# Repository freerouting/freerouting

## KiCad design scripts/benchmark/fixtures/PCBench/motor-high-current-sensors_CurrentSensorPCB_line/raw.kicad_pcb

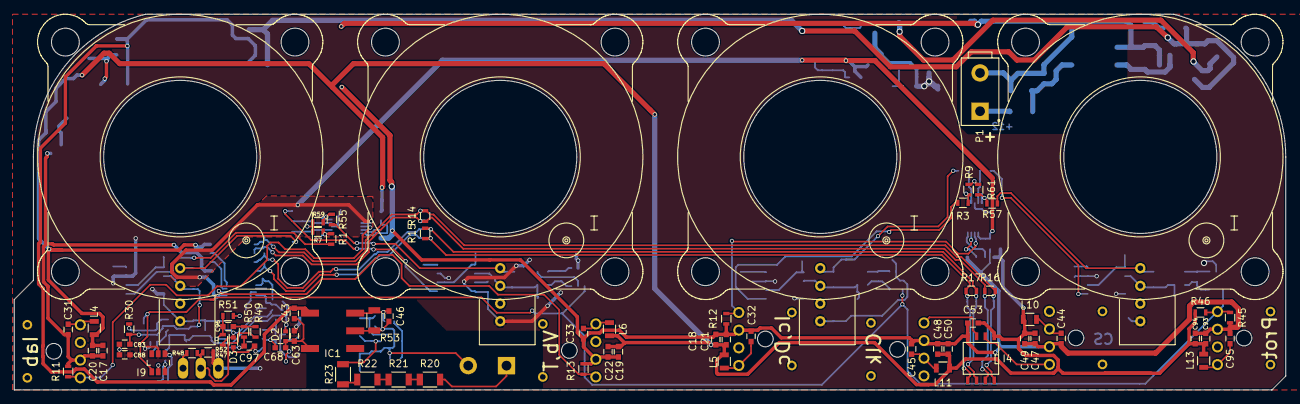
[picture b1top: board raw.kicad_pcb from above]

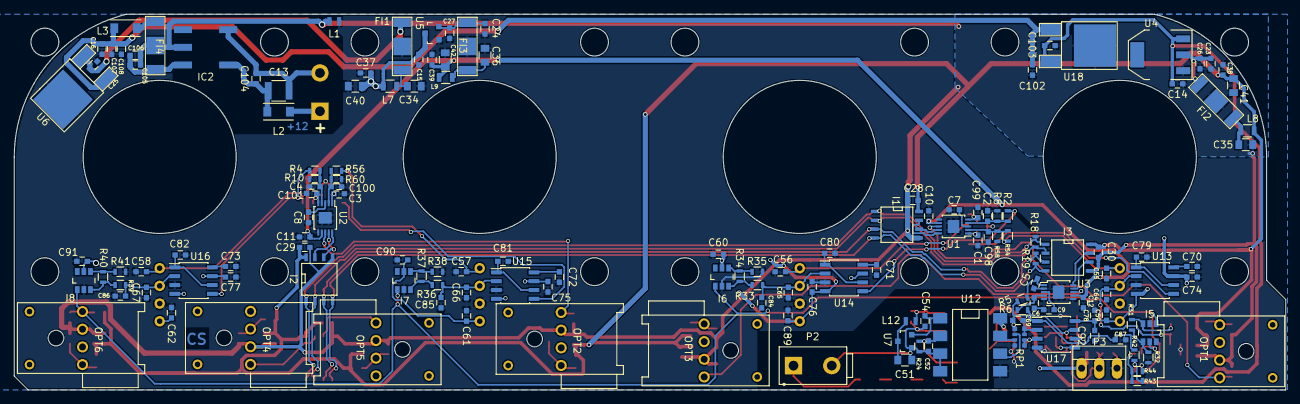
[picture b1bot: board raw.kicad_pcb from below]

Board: 2 copper layers, 182.8 x 54.0 mm, 222 parts (150 on the bottom side), 102 nets.

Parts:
C1, C2, C3, C4, C5, C6, C98, C99, C100, C101: 5.1n; C_0603
C7, C8, C9, C10, C11, C12, C20, C21, C22, C31, C32, C33, C44, C45, C47, C48, C94, C95: 10u; C_0603
C13: 22u, 16V; C_1210
C14, C15, C16, C17, C18, C19, C28, C29, C30, C43, C49, C50, C53, C74, C75, C76, C77, C79, C80, C81, C82, C88, C89, C90, C91, C92, C93, C102: 100n; C_0603
C23, C24, C25, C54, C103, C105, C107: 1u; C_0603
C26, C27, C46, C68, C69, C104, C106, C108: 1n; C_0603
C34, C35, C36: 10u, 6.3v; C_0805
C37, C38, C39, C52: 10n; C_0603
C40, C41, C42, C51: 4u7; C_0805
C55, C56, C57, C58, C59, C60, C61, C62, C63, C78, C83, C84, C85, C86, C87, C96, C97: 47n; C_0603
C64, C65, C66, C67: 4n7; C_0603
C70, C71, C72, C73: 27p; C_0603
D2, D3: 3.3V; SOD-523
FI1, FI2, FI3, FI4: NFE61P; EMI_Filter_murata
I1, I2, I3: DS90LV028A; SOIC-8-N
I4: DS90LV027A; SOIC-8-N
I5, I6, I7, I8, I9: ADCMP671; TSOT-6-MK06A
IC1, IC2: Murata_MTU1; MTU1_Murata_DCDC
L1: INDUCTOR_SMALL; Neosid_Inductor_SM0603CG
L2, L3: 10uH; Neosid_Inductor_SM1206
L4, L5, L6, L10, L11, L13: 1uH; R_0805
L7, L8, L9: ?; R_0805
L12: 10uH; Neosid_Inductor_SM0603CG
OPT1, OPT2, OPT3, OPT6: AFBR-1634Z; HFBR-xx3xZ
OPT4, OPT5: AFBR-26x; HFBR-xx3xZ
P1, P2: CONN_01X02; Connector_Header_2Way_39-29-3026
P3: CONN_01X03; PINHEAD1-3
R1, R2, R3, R4, R54, R55, R56, R57: 3.6k; R_0603
R5, R6: 51; R_0603
R7, R8, R9, R10, R58, R59, R60, R61: 6.8k; R_0603
R11, R12, R13, R46: 4k7; R_0603
R14, R15, R16, R17, R18, R19: 330; R_0603
R20, R21, R22, R23: 100k; R_1206
R24: 158; R_0603
R30, R33, R36, R39: 1k6; R_0603
R31, R34, R37, R40: 910; R_0603
R32, R35, R38, R41: 270; R_0603
R42, R43, R44, R45, R47, R48, R49, R50, R51: DNP; R_0603
R52: 0R; R_0603
R53: 270; R_1206
RP1: R_PACK4; ACAS0612
U1, U2: LTC1407-1; MSOP-10-1EP_3x3mm_Pitch0.5mm
U3: LTC1407; MSOP-10-1EP_3x3mm_Pitch0.5mm
U4: LD1117S33TR; SOT-223
U5: MCP1700T-330; SOT-23
U6, U18: MC78M05CDT; TO-252-2Lead
U7: MCP1700T-500; SOT-23
U8, U9, U10: HTFS800; HTFS-Series_LEM-HallEffektCurrentTransducer
U11: HTFS400; HTFS-Series_LEM-HallEffektCurrentTransducer
U12: ACPL-C870; DIP-8_SMD
U13, U14, U15, U16: MAX7480; SOIC-8_3.9x4.9mm_Pitch1.27mm
U17: OPA350; SOIC-8_3.9x4.9mm_Pitch1.27mm

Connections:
+3.3VADC: C10.2, C11.2, C12.2, C39.1, C42.1, L9.2, U1.7, U2.7, U3.7
+3V3: C17.2, C18.2, C19.2, C20.2, C21.2, C22.2, C28.2, C29.2, C30.2, C38.1, C41.1, C47.2, C48.2, C49.2, C50.2, C53.2, C93.2, C94.2, I1.8, I2.8, I3.8, I4.1, L4.1, L5.1, L6.1, L8.2, L10.1, L11.1, L13.1, R46.1
+5V: C14.1, C43.1, C103.1, IC1.1, U4.3, U18.3
+5VA: C15.1, C37.1, C40.1, C59.2, C60.2, C61.2, C62.2, C63.2, C74.1, C75.1, C76.1, C77.1, C78.1, C88.2, C89.2, C90.2, C91.2, C92.2, I5.5, I6.5, I7.5, I8.5, I9.5, L7.2, P3.1, R47.2, U5.3, U8.1, U9.1, U10.1, U11.1, U12.8, U13.4, U13.7, U14.4, U14.7, U15.4, U15.7, U16.4, U16.7, U17.8
+9V: C16.1, C102.1, C107.1, C108.1, L3.2, U6.1, U18.1
/ADC_Ck+: I1.3, I2.3, I3.3, I4.6, R15.2, R17.2, R19.2
/ADC_Ck-: I1.4, I2.4, I3.4, I4.5, R15.1, R17.1, R19.1
/ADC_Smp+: I1.2, I2.2, I3.2, I4.7, R14.1, R16.1, R18.1
/ADC_Smp-: I1.1, I2.1, I3.1, I4.8, R14.2, R16.2, R18.2
/I_U: R1.2, U13.5
/I_V: R2.2, U14.5
/I_W: R3.2, U15.5
/I_bus: R4.2, U16.5
/I_bus_sense: C67.1, C86.1, R39.2, U11.3, U16.2
/I_u_sense: C64.1, C83.1, R30.2, U8.3, U13.2
/I_v_sense: C65.1, C84.1, R33.2, U9.3, U14.2
/I_w_sense: C66.1, C85.1, R36.2, U10.3, U15.2
/Over_IV_prot: I5.1, I6.1, I7.1, I8.1, I9.1, OPT6.4, R45.2, R46.2
/T_coolant: D3.1, R6.2, R52.1, U17.7
/V_bus: C69.2, C87.1, D2.1, R5.2, R42.2, RP1.4, U17.1
/V_ref_U: C55.1, R54.1, U8.4
/V_ref_V: C56.1, R55.2, U9.4
/V_ref_W: C57.1, R56.1, U10.4
/V_ref_bus: C58.1, R57.2, U11.4
AGND: C1.1, C2.1, C3.1, C4.1, C5.1, C6.1, C7.2, C8.2, C9.2, C10.1, C11.1, C12.1, C15.2, C16.2, C24.2, C25.2, C27.2, C34.2, C36.2, C37.2, C39.2, C40.2, C42.2, C43.2, C55.2, C56.2, C57.2, C58.2, C59.1, C60.1, C61.1, C62.1, C63.1, C64.2, C65.2, C66.2, C67.2, C68.2, C70.2, C71.2, C72.2, C73.2, C74.2, C75.2, C76.2, C77.2, C78.2, C79.2, C80.2, C81.2, C82.2, C83.2, C84.2, C85.2, C86.2, C87.2, C88.1, C89.1, C90.1, C91.1, C92.1, C97.2, C98.2, C99.2, C100.2, C101.2, C107.2, C108.2, D2.2, D3.2, FI1.2, FI3.2, I5.2, I6.2, I7.2, I8.2, I9.2, IC1.3, L1.2, P3.3, R7.1, R8.1, R9.1, R10.1, R32.1, R35.1, R38.1, R41.1, R44.1, R48.1, R51.1, R58.1, R59.1, R60.1, R61.1, RP1.1, U1.6, U1.11, U2.6, U2.11, U3.2, U3.5, U3.6, U3.11, U5.1, U6.2, U8.2, U9.2, U10.2, U11.2, U12.5, U13.3, U14.3, U15.3, U16.3, U17.4
DGND: C14.2, C17.1, C18.1, C19.1, C20.1, C21.1, C22.1, C23.2, C26.2, C28.1, C29.1, C30.1, C31.1, C32.1, C33.1, C35.2, C38.2, C41.2, C44.1, C45.1, C47.1, C48.1, C49.1, C50.1, C53.1, C93.1, C94.1, C95.1, C102.2, C103.2, C105.2, C106.2, FI2.2, FI4.2, I1.5, I2.5, I3.5, I4.4, IC2.5, L1.1, OPT1.3, OPT2.3, OPT3.3, OPT4.2, OPT5.2, OPT6.3, R11.1, R12.1, R13.1, R45.1, U4.1, U18.2
unnamed: C1.2, R1.1, R7.2, U1.1
unnamed: C2.2, R2.1, R8.2, U1.4
unnamed: C3.2, R3.1, R9.2, U2.1
unnamed: C4.2, R4.1, R10.2, U2.4
unnamed: C5.2, R5.1, U3.1
unnamed: C6.2, R6.1, U3.4
unnamed: C7.1, U1.3
unnamed: C8.1, U2.3
unnamed: C9.1, U3.3
unnamed: C23.1, C26.1, FI2.1, U4.2
unnamed: C24.1, C27.1, FI3.1, U5.2
unnamed: C25.1, FI1.1, U6.3
unnamed: C31.2, L4.2, OPT1.1
unnamed: C32.2, L5.2, OPT2.1
unnamed: C33.2, L6.2, OPT3.1
unnamed: C34.1, FI1.3, L7.1
unnamed: C35.1, FI2.3, L8.1
unnamed: C36.1, FI3.3, L9.1
unnamed: C44.2, L10.2, OPT4.3
unnamed: C45.2, L11.2, OPT5.3
unnamed: C46.1, C51.2, C52.2, C54.2, IC1.5, P2.2, R24.2, R53.1, U7.1, U12.3, U12.4
unnamed: C46.2, IC1.6, L12.1, R53.2
unnamed: C51.1, L12.2, U7.3
unnamed: C52.1, R23.1, R24.1, U12.2
unnamed: C54.1, U7.2, U12.1
unnamed: C68.1, RP1.7, RP1.8, U17.3
unnamed: C69.1, RP1.5, RP1.6, U17.2
unnamed: C70.1, U13.8
unnamed: C71.1, U14.8
unnamed: C72.1, U15.8
unnamed: C73.1, U16.8
unnamed: C79.1, U13.1, U13.6
unnamed: C80.1, U14.1, U14.6
unnamed: C81.1, U15.1, U15.6
unnamed: C82.1, U16.1, U16.6
unnamed: C95.2, L13.2, OPT6.1
unnamed: C96.1, R51.2, R52.2, U17.6
unnamed: C96.2, R49.1, R50.2
unnamed: C97.1, R50.1, U17.5
unnamed: C98.1, R54.2, R58.2, U1.2
unnamed: C99.1, R55.1, R59.2, U1.5
unnamed: C100.1, R56.2, R60.2, U2.2
unnamed: C101.1, R57.1, R61.2, U2.5
unnamed: C13.2, C104.1, IC2.3, P1.2
unnamed: C13.1, C104.2, IC2.1, L2.2
unnamed: C105.1, C106.1, FI4.1, IC2.6
unnamed: FI4.3, L3.1
unnamed: I1.6, U1.9
unnamed: I1.7, U1.10
unnamed: I2.6, U2.9
unnamed: I2.7, U2.10
unnamed: I3.6, U3.9
unnamed: I3.7, U3.10
unnamed: I4.2, OPT4.1
unnamed: I4.3, OPT5.1
unnamed: I5.3, R30.1, R31.2
unnamed: I5.4, R31.1, R32.2
unnamed: I6.3, R33.1, R34.2
unnamed: I6.4, R34.1, R35.2
unnamed: I7.3, R36.1, R37.2
unnamed: I7.4, R37.1, R38.2
unnamed: I8.3, R39.1, R40.2
unnamed: I8.4, R40.1, R41.2
unnamed: I9.3, R42.1, R43.2
unnamed: I9.4, R43.1, R44.2
unnamed: L2.1, P1.1
unnamed: OPT1.4, R11.2, U1.8
unnamed: OPT2.4, R12.2, U2.8
unnamed: OPT3.4, R13.2, U3.8
unnamed: P2.1, R20.2
unnamed: P3.2, R47.1, R48.2, R49.2
unnamed: R20.1, R21.2
unnamed: R21.1, R22.2
unnamed: R22.1, R23.2
unnamed: RP1.2, U12.7
unnamed: RP1.3, U12.6

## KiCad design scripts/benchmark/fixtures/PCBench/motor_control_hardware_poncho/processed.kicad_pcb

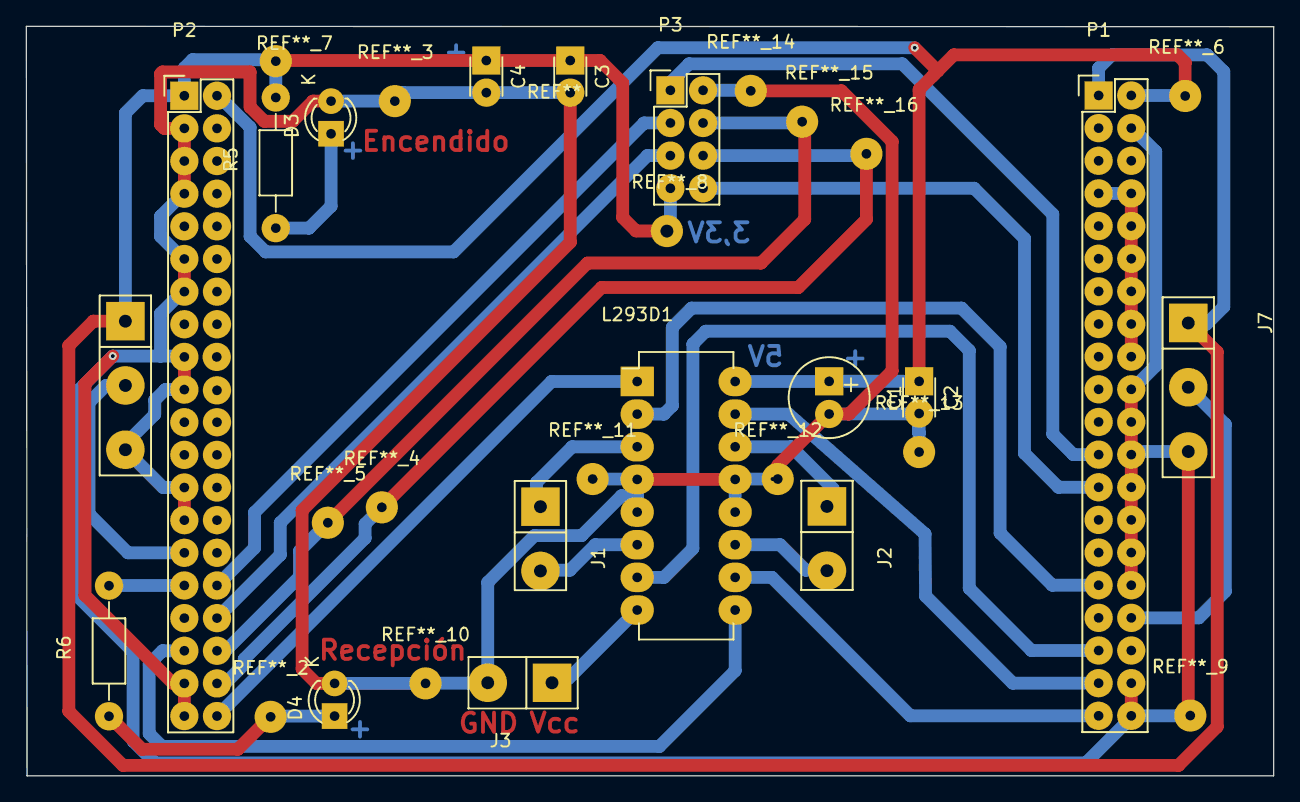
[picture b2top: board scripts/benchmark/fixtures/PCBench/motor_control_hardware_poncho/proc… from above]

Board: 2 copper layers, 97.0 x 58.3 mm, 17 parts (0 on the bottom side), 26 nets.

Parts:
C1: CP; Elko_vert_11.2x6.3mm_RM2.5
C2, C3, C4: C; C_Disc_D3_P2.5
D3, D4: LED; LED-3MM
J1, J2, J3: TB_1X2; bornera1x2
J6, J7: TB_1X3; bornera1x3
L293D1: L293D; DIP-16_W7.62mm_LongPads
P1, P2: CONN_20X2; Pin_Header_Straight_2x20
P3: ESP8266; Pin_Header_Straight_2x04
R5, R6: R; Resistor_Horizontal_RM10mm

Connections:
+3V3: C3.1, C4.1, J6.1, J7.1, P1.1, P2.1, P3.4, R5.2
+5V: C1.1, C2.1, L293D1.16, P1.2, P2.2
/ENG0_OUT0: J1.1, L293D1.3
/ENG0_OUT1: J1.2, L293D1.6
/ENG1_OUT0: J2.1, L293D1.14
/ENG1_OUT1: J2.2, L293D1.11
/GPIO0: J6.2, P2.29
/GPIO1: P2.32, P3.2
/GPIO2: P2.31, R6.2
/GPIO3: P2.34, P3.3
/GPIO5: P2.36, P3.7
/GPIO6: L293D1.9, P2.35
/GPIO7: P2.38, P3.6
/GPIO8: L293D1.1, P2.40
/MOTOR_VCC: J3.1, L293D1.8
/RS232_RXD: P1.23, P3.1
/RS232_TXD: P1.25, P3.5
/TEC_COL0: L293D1.10, P1.39
/TEC_COL1: L293D1.2, P1.31
/TEC_COL2: J7.2, P1.34
/TEC_F2: L293D1.15, P1.37
/TEC_F3: L293D1.7, P1.35
GND: C1.2, C2.2, C3.2, C4.2, D3.1, D4.1, J3.2, J6.3, J7.3, L293D1.4, L293D1.5, L293D1.12, L293D1.13, P1.4, P1.20, P1.22, P1.24, P1.26, P1.28, P1.30, P1.32, P1.38, P1.40, P2.3, P2.5, P2.7, P2.11, P2.13, P2.17, P2.19, P2.25, P2.27, P2.37, P2.39, P3.8
GNDA: P1.7, P1.8, P1.10, P1.12, P1.14, P1.16, P1.18
unnamed: D3.2, R5.1
unnamed: D4.2, R6.1

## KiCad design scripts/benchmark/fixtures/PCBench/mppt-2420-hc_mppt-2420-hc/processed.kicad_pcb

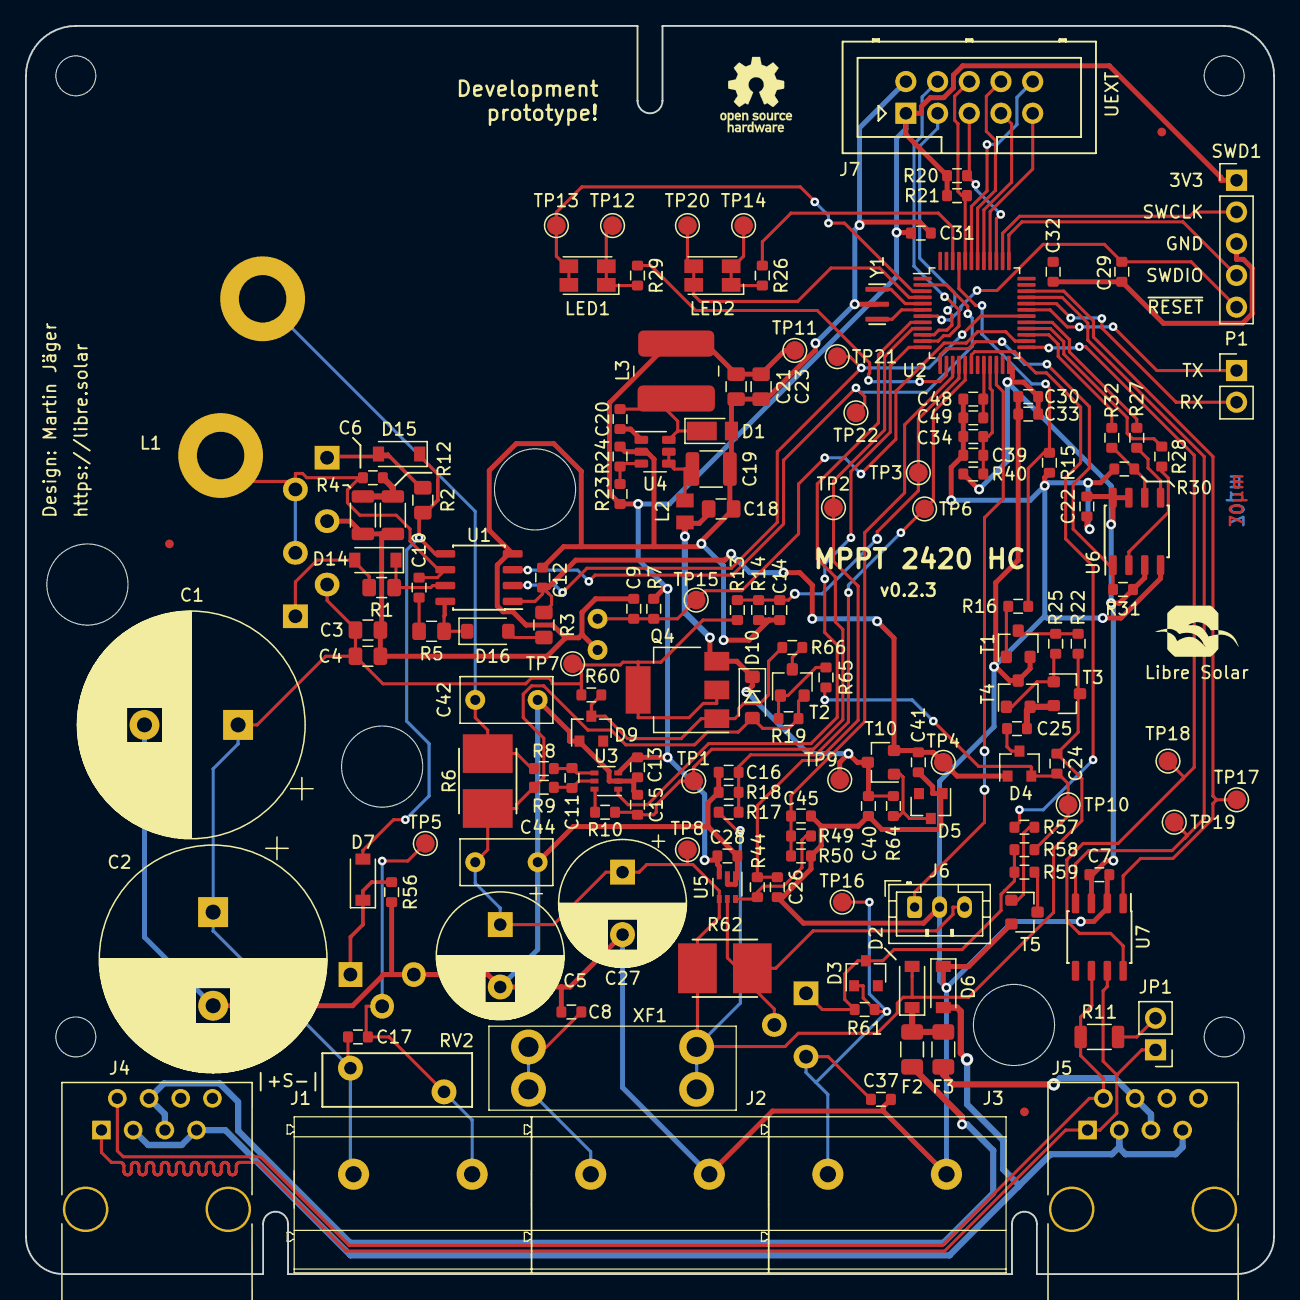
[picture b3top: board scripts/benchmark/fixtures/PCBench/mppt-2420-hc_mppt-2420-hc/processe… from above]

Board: 4 copper layers, 100.0 x 100.0 mm, 172 parts (0 on the bottom side), 94 nets.

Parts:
C1, C2: 390µF; CP_Radial_D18.0mm_P7.50mm
C3, C18: 1µF; C_0805_2012
C4: 100nF; C_0805_2012
C5, C27: 680µF; CP_Radial_D10.0mm_P5.00mm
C6: 2.2nF; C_0603_1608
C7, C9, C10, C13, C20, C22, C24, C28, C29, C30, C31, C32, C48: 100nF; C_0603_1608
C8, C14, C16, C17, C25, C26, C34, C37, C45: 10nF; C_0603_1608
C11, C15: 1nF; C_0603_1608
C12, C33, C39, C49: 2.2µF; C_0603_1608
C19: 4.7µF; C_1210_3225
C21, C23: 10µF; C_0805_2012
C40: 1µF; C_0603_1608
C41: 4.7µF; C_0603_1608
C42, C44: 0.22µF; C_Rect_L7.2mm_W3.5mm_P5.00mm_FKS2_FKP2_MKS2_MKP2
D1: SS16FP; D_PowerDI-123
D2, D6: NRVTS260ESFT1G; D_SOD-123
D3, D5: 12V; D_SOT-23_ANK
D4: BAS70-04; SOT-23
D7, D14, D15: SS14FL; D_SOD-123
D9: 47V; D_SOT-23_ANK
D10, D16: 1N4148; D_SOD-123
F1: 25A; NULL
F2, F3: 500mA; Fuse_1206_3216Metric
FID1, FID2, FID3: Fiducial; Fiducial_0.7mm
J1, J2, J3: MKDS 5/ 2-9,5; Phoenix_Contact_MKDS_5-2-9,5
J4, J5: 8P8C; RJ45_8P8C
J6: JST PH; JST_PH_B3B-PH-K_1x03_P2.00mm_Vertical
J7: UEXT; Box_Header_2x05x2.54mm_Straight
JP1: Jumper_NC_Small; PinHeader_1x02_P2.54mm_Vertical
L1: 53µH; Inductor_Toroid_D32.8mm_4mm2
L2: 4.7µH; L_0805_2012Metric
L3: 47µH; Bourns_SRN6045TA
LED1, LED2: LED_Dual_PLCC4; LED_Avago_PLCC4_3.2x2.8mm_CW
LOGO1: LIBRE_SOLAR; LIBRESOLAR_LOGO
LOGO2: OPEN_HARDWARE; OSHW-Logo_5.7x6mm_SilkScreen
MK1, MK2, MK3, MK4: Mounting_Hole; MountingHole_3.2mm_M3
P1: CONN_01X02; PinHeader_1x02_P2.54mm_Vertical
Q1, Q2, Q3, Q7: IPA045N10N3G; TO-220-3_Horizontal_BottomHeatsink
Q4: BUK98180-100A; SOT-223-3_TabPin2
R1, R2, R3, R5: 3R3; R_0805_2012
R4, R12: 4R7; R_1206_3216
R6, R62: 2m; R_Bourns_CRE2512
R7, R16, R19, R24, R49, R59, R64: 10k; R_0603_1608
R8, R9: 10R; R_0603_1608
R10, R25, R26, R29, R66: 1k; R_0603_1608
R11: 120R; R_1206_3216
R13, R17, R22, R30, R58, R60, R65: 100k; R_0603_1608
R14, R20, R21, R31, R44, R57: 2.2k; R_0603_1608
R15, R56, R61: 1M; R_0603_1608
R18: 5.6k; R_0603_1608
R23: 33k; R_0603_1608
R27, R28, R32, R40: 47R; R_0603_1608
R50: 8.2k; C_0603_1608
RT1: 10k; C_Disc_D3.8mm_W2.6mm_P2.50mm
RV2: 82V; RV_Disc_D12mm_W4.3mm_P7.5mm
SWD1: ST_Nucleo_SWD; PinHeader_1x05_P2.54mm_Vertical
T1, T2, T3, T5, T10: BC846B; SOT-23
T4: BC856B; SOT-23
TP1, TP2, TP3, TP4, TP5, TP6, TP7, TP8, TP9, TP10, TP11, TP12, TP13, TP14, TP15, TP16, TP17, TP18, TP19, TP20, TP21, TP22: 1.5mm; TestPoint_Pad_D1.5mm
U1: LM5107; SOIC-8_3.9x4.9mm_Pitch1.27mm
U2: STM32G431CBTx; LQFP-48_7x7mm_P0.5mm
U3, U5: INA186; SOT-363_SC-70-6
U4: LMR16006X; SOT-23-6
U6: W25Q80DVS; SOIC-8_3.9x4.9mm_Pitch1.27mm
U7: TCAN334; SOIC-8_3.9x4.9mm_Pitch1.27mm
XF1: Fuse_Holder; Keystone-Fuse-3557-2
Y1: 8MHz; Resonator_Murata_CSTNE

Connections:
+3V3: C7.1, C13.1, C21.1, C22.1, C23.1, C28.1, C30.1, C31.1, C33.1, J7.1, L3.2, R7.1, R20.2, R21.2, R23.1, R31.2, R40.2, SWD1.1, TP11.1, U2.24, U3.3, U5.3, U6.3, U6.7, U6.8, U7.3
+12V: C12.1, C41.1, D4.1, R3.2, T10.2, TP4.1, U1.1
/BAT+: C8.1, J2.1, XF1.2
/CAN/CAN_PWR1: F2.1, J4.4, J4.5
/CAN/CAN_PWR2: F3.1, J5.4, J5.5
/CAN/CAN_RX: TP19.1, U2.33, U7.4
/CAN/CAN_STB: TP18.1, U2.25, U7.8
/CAN/CAN_TX: TP17.1, U2.34, U7.1
/CAN_GND: D6.2, J4.3, J4.7, J5.3, J5.7
/CAN_H: J4.1, J5.1, JP1.1, U7.7
/CAN_L: J4.2, J5.2, R11.2, U7.6
/DC/DC/HS_DRV: D14.1, R1.2, U1.7
/DC/DC/LS_DRV: D7.2, D15.1, R2.2, U1.5
/DC/DC/PWM_HS: TP21.1, U1.2, U2.30
/DC/DC/PWM_LS: TP22.1, U1.3, U2.2
/DC/DC/SHUNT_DCDC_P: C42.1, L1.2, R6.2, R8.1
/DC/DC/SW_NODE: C6.1, C10.2, L1.1, Q1.3, Q2.2, U1.6
/DCDC_HV+: C1.1, C2.1, C3.1, C4.1, C17.1, J1.1, Q1.2, Q4.2, R13.1, R60.2, RV2.1, TP7.1
/DCDC_HV-: C17.2, J1.2, Q3.2, RV2.2, TP5.1
/LOAD+: C37.1, D3.2, J3.1, Q7.3, R61.2, TP16.1
/Load switch/CP_OUT: C24.1, D4.2, R58.1, R65.2, TP10.1
/MCU/ADC1_IN11: C9.1, R7.2, RT1.1, TP15.1, U2.26
/MCU/ADC1_IN12: C16.1, R17.2, R18.1, TP6.1, U2.17
/MCU/ADC1_IN15: C14.1, R13.2, R14.1, TP3.1, U2.16
/MCU/ADC12_IN1: C15.1, R10.2, TP1.1, U2.8
/MCU/ADC12_IN2: C26.1, R44.2, TP2.1, U2.9
/MCU/COMP2_INP: C45.1, R49.1, R50.2, U2.15
/MCU/DAC1: U2.12, U3.1
/MCU/GPIOB_2: R57.1, U2.18
/MCU/GPIOC_14: LED1.2, LED1.3, TP13.1, U2.3
/MCU/GPIOC_15: LED2.2, LED2.3, TP20.1, U2.4
/MCU/I2C1_SCL: J7.5, R20.1, U2.39
/MCU/I2C1_SDA: J7.6, R21.1, U2.44
/MCU/OSC_IN: U2.5, Y1.3
/MCU/OSC_OUT: U2.6, Y1.1
/MCU/SPI1_MISO: J7.7, U2.41
/MCU/SPI1_MOSI: J7.8, U2.42
/MCU/SPI1_SCK: J7.9, U2.40
/MCU/SPI1_SSEL: J7.10, U2.43
/MCU/SPI2_CS: R31.1, U2.13, U6.1
/MCU/SPI2_MISO: R28.1, U2.28
/MCU/SPI2_MOSI: R27.1, U2.29
/MCU/SPI2_SCK: R32.2, U2.27
/MCU/SWCLK: SWD1.2, U2.38
/MCU/SWDIO: SWD1.4, U2.37
/MCU/TIM16_CH1: R29.2, U2.14
/MCU/TIM17_CH1: R26.2, U2.46
/MCU/USART1_RX: P1.2, U2.32
/MCU/USART1_TX: P1.1, U2.31
/MCU/USART2_RX: J7.4, U2.11
/MCU/USART2_TX: J7.3, U2.10
/MCU/~RESET: C29.1, SWD1.5, U2.7
/MEAS_LV+: J6.3, Q7.2, R62.1, U5.5
/PWR_INFO: J6.1, U2.22
/Power supply/CP_PWM: R15.2, R16.2, U2.45
/Power supply/CP_SW: C25.2, T3.2, T4.2
/Power supply/SUPPLY_INPUT: C18.1, C40.1, D10.1, L2.1, Q4.3, R64.2, T10.3, TP9.1
GND: C1.2, C2.2, C3.2, C4.2, C5.2, C7.2, C8.2, C9.2, C12.2, C13.2, C14.2, C15.2, C16.2, C18.2, C19.2, C21.2, C22.2, C23.2, C26.2, C27.2, C28.2, C29.2, C30.2, C31.2, C32.2, C33.2, C34.2, C37.2, C39.2, C40.2, C41.2, C42.2, C44.1, C45.2, C48.2, C49.2, D1.2, D5.2, D6.1, D9.2, J2.2, J3.2, J6.2, J7.2, Q2.3, Q3.3, R4.1, R12.1, R14.2, R15.1, R18.2, R24.2, R30.1, R50.1, R56.2, RT1.2, SWD1.3, T1.2, T4.3, T5.2, U1.4, U3.2, U4.2, U5.1, U5.2, U6.4, U7.2, Y1.2
unnamed: C6.2, R4.2, R12.2
unnamed: C10.1, R5.2
unnamed: C11.1, R8.2, U3.4
unnamed: C11.2, R9.2, U3.5
unnamed: C19.1, L2.2, U4.4, U4.5
unnamed: C20.1, U4.1
unnamed: C20.2, D1.1, L3.1, U4.6
unnamed: C25.1, D4.3
unnamed: D2.1, F2.2, F3.2
unnamed: D3.1, Q7.1, R58.2, R59.2, R61.1
unnamed: D5.1, R64.1, T10.1
unnamed: D7.1, Q3.1, R56.1
unnamed: D9.1, Q4.1, R60.1, R66.2
unnamed: D14.2, Q1.1, R1.1
unnamed: D15.2, Q2.1, R2.1
unnamed: D16.1, R5.1, U1.8
unnamed: D16.2, R3.1
unnamed: JP1.2, R11.1
unnamed: LED1.1, LED1.4, R29.1, TP12.1
unnamed: LED2.1, LED2.4, R26.1, TP14.1
unnamed: R10.1, U3.6
unnamed: R16.1, T1.1
unnamed: R19.2, R65.1, T2.1
unnamed: R22.1, R25.1, T1.3
unnamed: R23.2, R24.1, U4.3
unnamed: R25.2, T3.1, T4.1
unnamed: R27.2, U6.5
unnamed: R28.2, U6.2
unnamed: R30.2, R32.1, U6.6
unnamed: R44.1, R49.2, U5.6
unnamed: R57.2, T5.1
unnamed: R59.1, T5.3
unnamed: R66.1, T2.3
VBUS: C5.1, C24.2, C27.1, C44.2, D2.2, D10.2, R6.1, R9.1, R17.1, R19.1, R22.2, R62.2, T2.2, T3.3, TP8.1, U5.4, XF1.1
VDDA: C34.1, C39.1, R40.1, U2.21
VREF: C48.1, C49.1, U2.20

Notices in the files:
scripts/benchmark/fixtures/PCBench/mppt-2420-hc_mppt-2420-hc/processed.kicad_pcb:
Licensed under CERN-OHL-W version 2
